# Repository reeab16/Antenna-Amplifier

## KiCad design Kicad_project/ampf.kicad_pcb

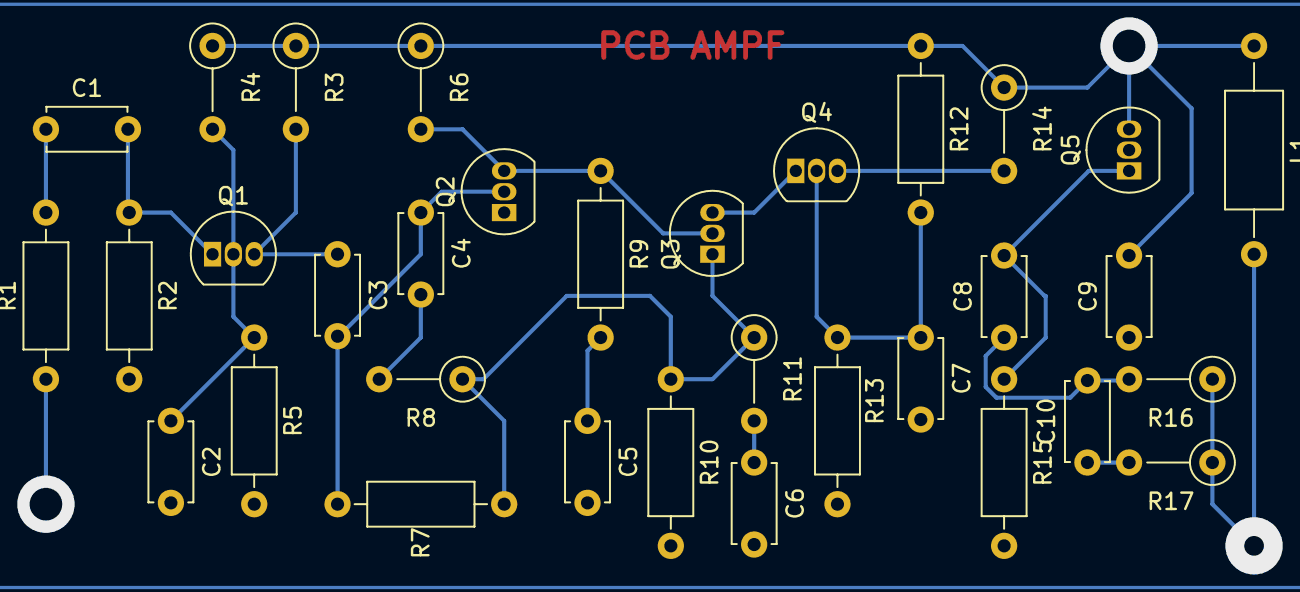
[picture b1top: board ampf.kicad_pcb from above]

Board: 2 copper layers, 33 parts (0 on the bottom side), 18 nets.

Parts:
C1, C2, C3, C5, C6, C7, C8: 10nF; C_Disc_D4.7mm_W2.5mm_P5.00mm
C4: 1pF; C_Disc_D4.7mm_W2.5mm_P5.00mm
C9: 100nF; C_Disc_D4.7mm_W2.5mm_P5.00mm
C10: 4.7pF; C_Disc_D4.7mm_W2.5mm_P5.00mm
L1: L_Axial_L7.0mm_D3.3mm_P12.70mm_Horizontal_Fastron_MICC
Q1, Q2, Q3, Q4, Q5: 2N3904; TO-92_Inline
R1: 68; R_Axial_DIN0207_L6.3mm_D2.5mm_P10.16mm_Horizontal
R2, R15: 560; R_Axial_DIN0207_L6.3mm_D2.5mm_P10.16mm_Horizontal
R3, R6: 680; R_Axial_DIN0207_L6.3mm_D2.5mm_P5.08mm_Vertical
R4: 1.5k; R_Axial_DIN0207_L6.3mm_D2.5mm_P5.08mm_Vertical
R5: 1k; R_Axial_DIN0207_L6.3mm_D2.5mm_P10.16mm_Horizontal
R7: 390; R_Axial_DIN0207_L6.3mm_D2.5mm_P10.16mm_Horizontal
R8: 33; R_Axial_DIN0207_L6.3mm_D2.5mm_P5.08mm_Vertical
R9: 270; R_Axial_DIN0207_L6.3mm_D2.5mm_P10.16mm_Horizontal
R10: 100; R_Axial_DIN0207_L6.3mm_D2.5mm_P10.16mm_Horizontal
R11: 56; R_Axial_DIN0207_L6.3mm_D2.5mm_P5.08mm_Vertical
R12, R13: 2.2k; R_Axial_DIN0207_L6.3mm_D2.5mm_P10.16mm_Horizontal
R14: 150; R_Axial_DIN0207_L6.3mm_D2.5mm_P5.08mm_Vertical
R16, R17: 68; R_Axial_DIN0207_L6.3mm_D2.5mm_P5.08mm_Vertical

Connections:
GND: C2.2, C5.2, C6.2, C7.2, C9.1, Q2.1 (E), R2.2, R5.2, R10.2, R13.2, R15.2
unnamed: C2.1, Q1.2 (B), R4.2, R5.1
unnamed: C3.2, C4.1, Q2.2 (B), R7.2
unnamed: C3.1, Q1.3 (C), R3.2
unnamed: Q3.1 (E), R7.1, R8.1, R10.1, R11.1
unnamed: C7.1, Q4.2 (B), R12.2, R13.1
unnamed: Q3.3 (C), Q4.1 (E)
unnamed: C8.2, Q4.3 (C), Q5.1 (E), R14.2, R15.1
unnamed: C9.2, L1.1, Q5.3 (C), R3.1, R4.1, R6.1, R12.1, R14.1
c101: C10.1, R17.2
c102: C8.1, C10.2, R16.2
lll: L1.2, R16.1, R17.1
net2: C1.1, R1.2
net-c5: C5.1, R9.2
net-c6: C6.1, R11.2
net-q: Q2.3 (C), Q3.2 (B), R6.2, R9.1
netc2: C1.2, Q1.1 (E), R2.1
netx: C4.2, R8.2

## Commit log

2022-06-10 The PCB and Schem of the Amplifier
2022-06-10 SPICE simulation
    Also the value i used and the forms
